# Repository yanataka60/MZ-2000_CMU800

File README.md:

# MZ-2000用CMU-800インタフェース基板

#### 2025.12.25追記)CMU-800インタフェース基板とEMMを合体させたEMM基板も作りました。

https://github.com/yanataka60/EMM_for_MZ-2000

　MZ-2000拡張ユニットに挿入できるCMU-800インタフェース基板を作ってみました。

　MZ-2000及びMZ-2200用として作成していますが、MZ-80B、MZ-2500もカードスロットの規格は同じなので使えると思います。

　スロットカバーを取り付けるとスロットカバーの穴がスロットより若干上にずれているため基板が上反り気味になりますが、動作に支障はないようです。

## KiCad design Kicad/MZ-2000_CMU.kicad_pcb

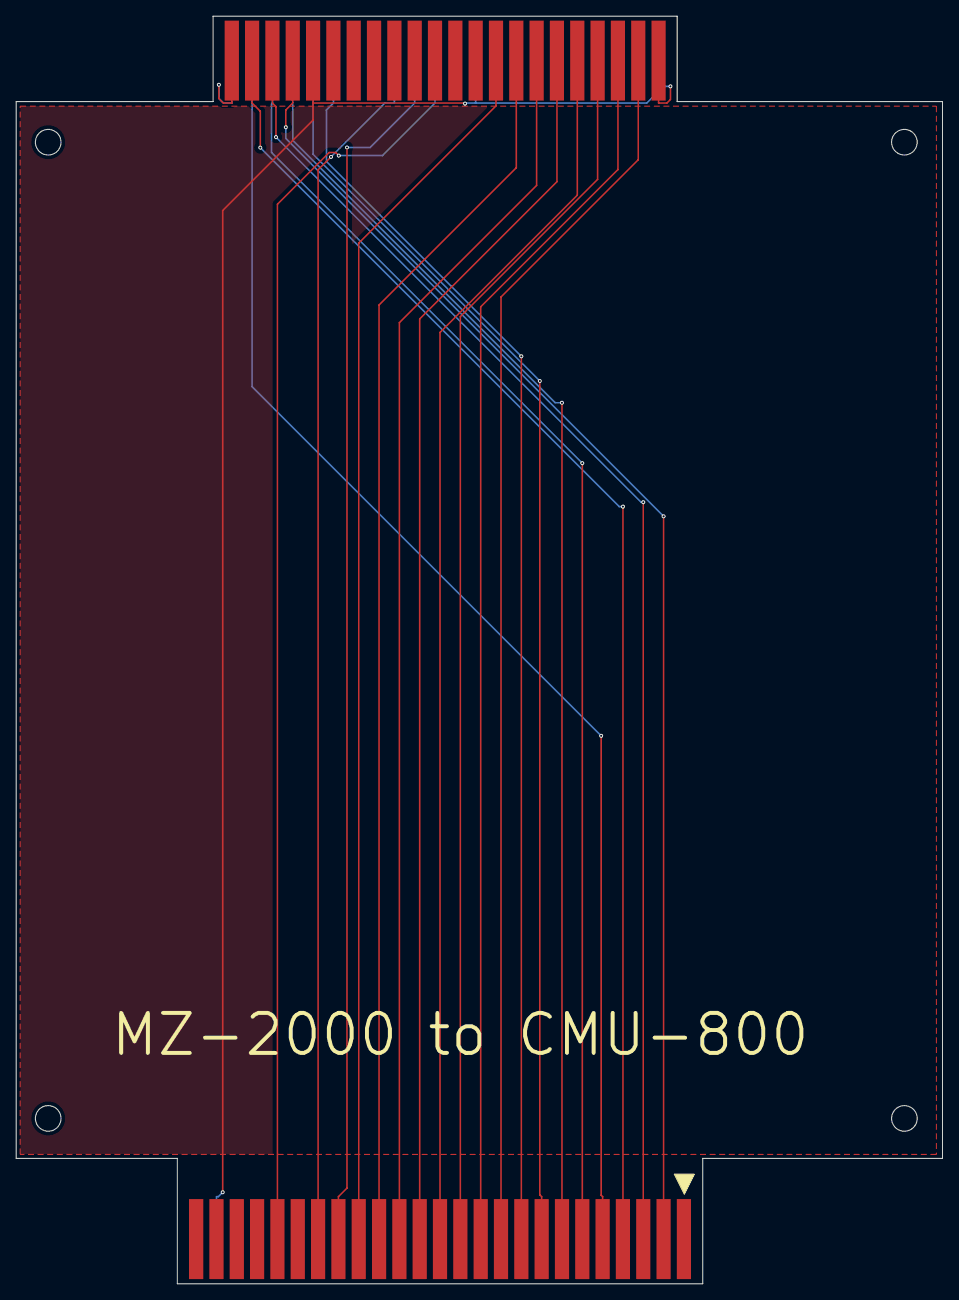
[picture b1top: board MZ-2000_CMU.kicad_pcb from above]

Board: 2 copper layers, 115.8 x 158.4 mm, 6 parts (1 on the bottom side), 21 nets.

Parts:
J1: Conn_02x22_Row_Letter_First; BUS_MZ2000
J2: Conn_02x25_Odd_Even; BUS_50Pin
MH1, MH2, MH3, MH4: MountingHole_3.2mm_M3

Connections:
+5V: J1.a1, J1.b1
/A0: J1.a21, J2.19
/A1: J1.a20, J2.21
/A2: J1.a19, J2.23
/A3: J1.a18, J2.25
/A4: J1.a17, J2.27
/A5: J1.a16, J2.29
/A6: J1.a15, J2.31
/A7: J1.a14, J2.33
/D0: J1.a4, J2.3
/D1: J1.a3, J2.5
/D2: J1.a2, J2.7
/D3: J1.b2, J2.9
/D4: J1.b3, J2.11
/D5: J1.b4, J2.13
/D6: J1.b5, J2.15
/D7: J1.b6, J2.17
/~IOREQ: J1.b11, J2.41
/~RD: J1.b10, J2.35
/~WR: J1.b9, J2.37
GND: J1.a5, J1.a22, J1.b13, J1.b22, J2.48
